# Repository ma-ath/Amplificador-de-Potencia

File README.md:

# Amplificador-de-Potencia
Trabalho Final de Eletrônica IV - Amplificador de Potência

エレクトロニクス4期末宿題、パワー増幅器

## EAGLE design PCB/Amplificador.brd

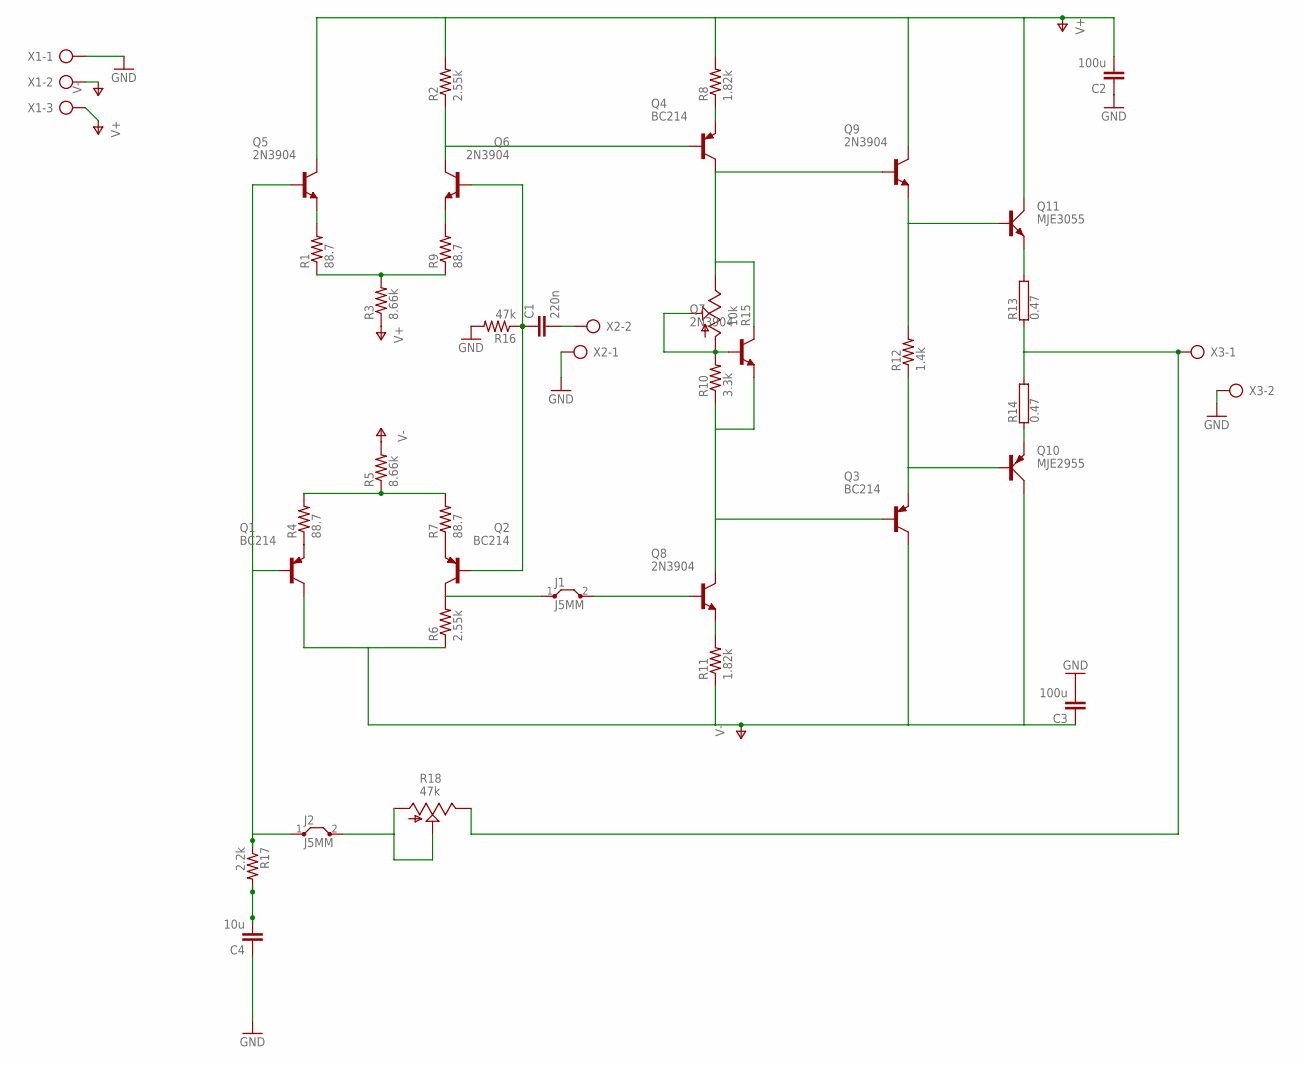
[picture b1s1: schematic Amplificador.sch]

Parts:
C1: 220n; C5B2.5
C2, C3: 100u; C5B2.5
C4: 10u; C5B2.5
J1, J2: J5MM; 05
Q1, Q2, Q3, Q4: BC214; TO92
Q5, Q6, Q7, Q8, Q9: 2N3904; TO92
Q10: MJE2955; TO220AV
Q11: MJE3055; TO220AV
R1, R4, R7, R9: 88.7; 0207/10
R2, R6: 2.55k; 0207/10
R3, R5: 8.66k; 0207/10
R8, R11: 1.82k; 0207/10
R10: 3.3k; 0207/10
R12: 1.4k; 0207/10
R13, R14: 0.47; CA4055
R15: 10k; CA6V
R16: 47k; 0207/10
R17: 2.2k; 0207/10
R18: 47k; CA6H
X1: AK500/3-H
X2, X3: AK500/2-H

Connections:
GND: C2.1, C3.2, C4.1, R16.2, X1.1, X2.1, X3.2
unnamed: R4.2, R5.1, R7.2
unnamed: J1.2, Q8.2 (B)
unnamed: Q3.1 (E), Q10.B, R12.1
unnamed: Q5.3 (E), R1.2
unnamed: Q4.2 (B), Q6.1 (C), R2.1
unnamed: Q8.3 (E), R11.2
unnamed: Q4.3 (C), Q7.1 (C), Q9.2 (B), R15.E
unnamed: Q7.2 (B), R10.2, R15.A, R15.S
unnamed: R1.1, R3.2, R9.1
unnamed: Q6.3 (E), R9.2
unnamed: Q1.1 (E), R4.1
unnamed: Q2.1 (E), R7.1
unnamed: C1.2, X2.2
unnamed: C1.1, Q2.2 (B), Q6.2 (B), R16.1
unnamed: R13.1, R14.2, R18.E, X3.1
unnamed: Q3.2 (B), Q7.3 (E), Q8.1 (C), R10.1
unnamed: Q4.1 (E), R8.1
unnamed: C4.2, R17.2
unnamed: J2.2, R18.A, R18.S
unnamed: Q9.3 (E), Q11.B, R12.2
unnamed: Q11.E, R13.2
unnamed: Q10.E, R14.1
unnamed: J1.1, Q2.3 (C), R6.2
unnamed: J2.1, Q1.2 (B), Q5.2 (B), R17.1
V+: C2.2, Q5.1 (C), Q9.1 (C), Q11.C, R2.2, R3.1, R8.2, X1.3
V-: C3.1, Q1.3 (C), Q3.3 (C), Q10.C, R5.2, R6.1, R11.1, X1.2

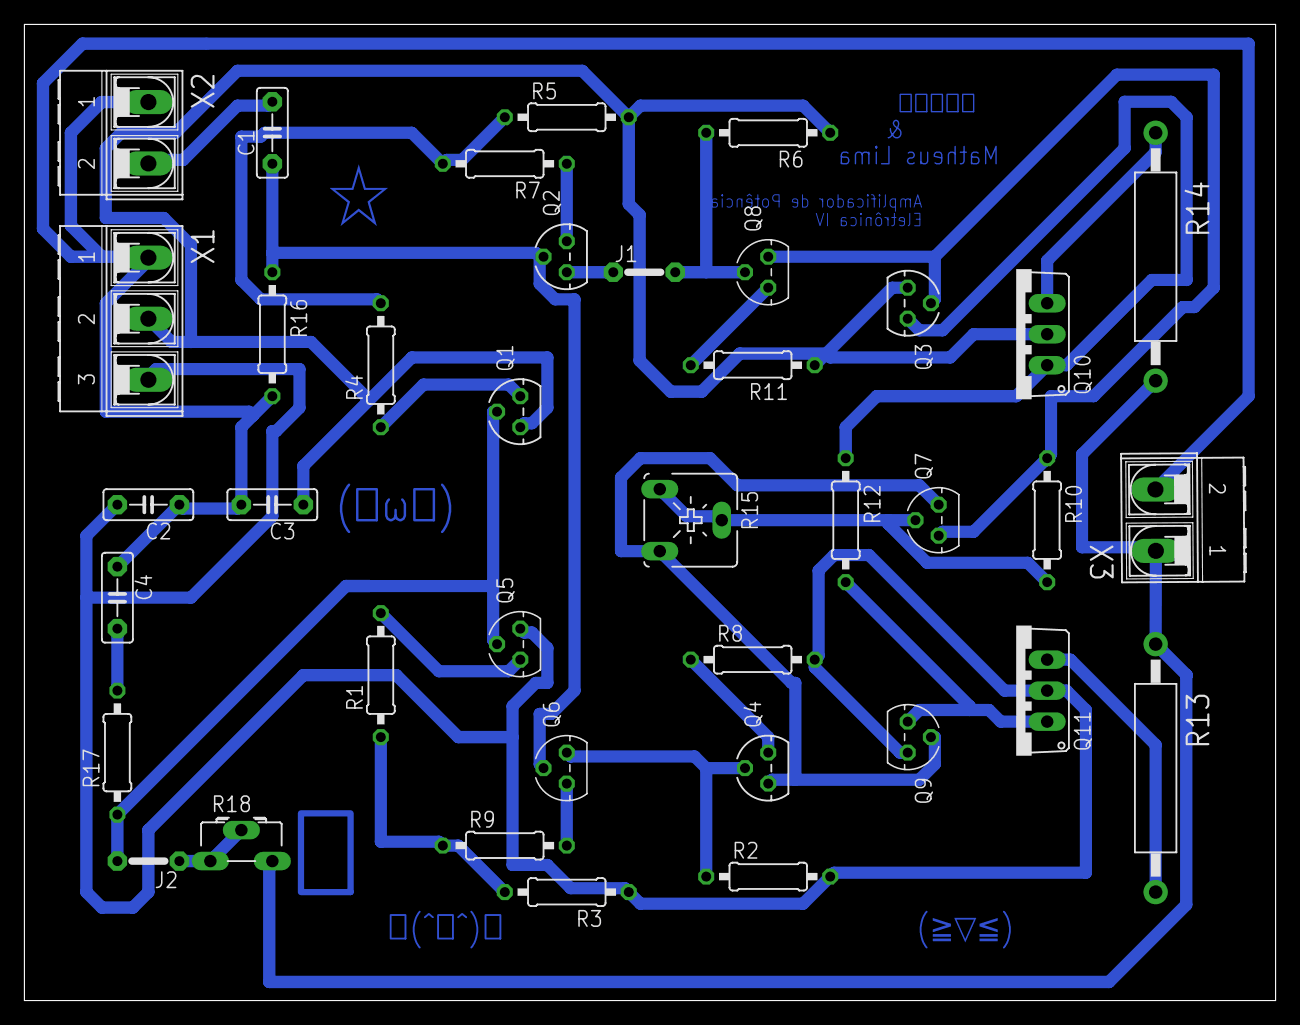
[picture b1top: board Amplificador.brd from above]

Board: 2 copper layers, 102.5 x 80.0 mm, 38 parts (0 on the bottom side), 27 nets.

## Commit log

2017-10-08 Arquivos Amplificador de Potência
    Criado o repositório, e adicionado todos os arquivos até então criados para o trabalho do Amplificador de Potência - Eletrônica IV
2017-10-08 Mudada a PCB
    Adicionado Nomes e Carinhas na PCB!
2017-10-09 hgf
    tgrfgt
2017-10-10 Placa Versão 2.0
    Talvez a versão final, compatível com nossos componentes comprados
2017-10-10 Trabalho de eletrônica versão 2.1
    Agora sim talvez a versão final, a anterior estava com erro
2017-10-24 Amplificador Final!
    PCI Final + PDFs para impressao
2017-10-24 PDFs
    Agora em Preto
2017-10-25 asdsdas
    awsdrweds
2017-11-21 ultimo update?
    ?
